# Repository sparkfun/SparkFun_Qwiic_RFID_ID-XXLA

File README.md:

SparkFun Qwiic RFID ID-XXLA
========================================

<table class="table table-hover table-striped table-bordered">
  <tr align="center">
   <td></td>
   <td></td>
  </tr>
  <tr align="center">
    <td><i>SparkFun RFID Qwiic Reader [<a href="https://www.sparkfun.com/products/15191">SEN-15191</a>]</i></td>
    <td><i>SparkFun RFID Qwiic Reader Kit [<a href="https://www.sparkfun.com/products/15209">KIT-15209</a>]<i></td>
  </tr>
</table>
     
The SparkFun Qwiic RFID ID-XXLA is a simple board that pairs with the ID-3LA, ID-12LA, ID-20LA, RFID modules.Utilizing the onboard ATtiny84A, the Qwiic RFID takes the six byte ID tag of your 125Khz RFID card, attaches a time stamp to it, and puts it onto a stack that holds up to 20 unique RFID scans at any given time. This information is easy to get at with some simple I2C commands and we’ve included some example code that shows you just how to do it using the broken out interrupt pin. We’ve also broken out two antennae pins that should only be used with the smaller ID-3LA.

The SparkFun Qwiic RFID has a buzzer and LED that indicates that card has been scanned. We’ve included a jumper to disconnect the buzzer, a jumper for the I2C pull-up resistors, an interrupt jumper, and finally an address jumper. The Qwiic RFID comes fully decked out in Qwiic connectors, no need to solder a thing, just plug it in and start scanning!

Repository Contents
-------------------

* **/Firmware** - The core sketch that runs the SparkFun Qwiic RFID ID-XXLA
* **/Arduino Examples** - A number of examples to show how to read buttons with time, change the I2C address and scan for I2C devices
* **/ATtiny Firmware** - Default firmware for the Qwiic RFID
* **/Hardware** - Eagle design files (.brd, .sch)

Documentation
--------------

* **[Hookup Guide](https://learn.sparkfun.com/tutorials/sparkfun-qwiic-rfid-idxxla-hookup-guide)** - Basic hookup guide.

Arduino Library 
----------------
* **[SparkFun Qwiic RFID Arduino Library](https://github.com/sparkfun/SparkFun_Qwiic_RFID_Arduino_Library)**

Python Package
----------------
* **[SparkFun Qwiic RFID Python Package](https://github.com/sparkfun/Qwiic_RFID_Py)**

Product Versions
----------------
* [SEN-15191](https://www.sparkfun.com/products/15191)- SparkFun Qwiic RFID ID-XXLA
* [KIT-15209](https://www.sparkfun.com/products/15209)- SparkFun Qwiic RFID ID-XXLA with ID Innovations RFID Module, Qwiic Cable, and RFID Tagged Cards, 

License Information
-------------------

This product is _**open source**_! 

Please review the LICENSE.md file for license information. 

If you have any questions or concerns on licensing, please contact techsupport@sparkfun.com.

Please use, reuse, and modify these files as you see fit. Please maintain attribution to SparkFun Electronics and release any derivative under the same license.

Distributed as-is; no warranty is given.

- Your friends at SparkFun.

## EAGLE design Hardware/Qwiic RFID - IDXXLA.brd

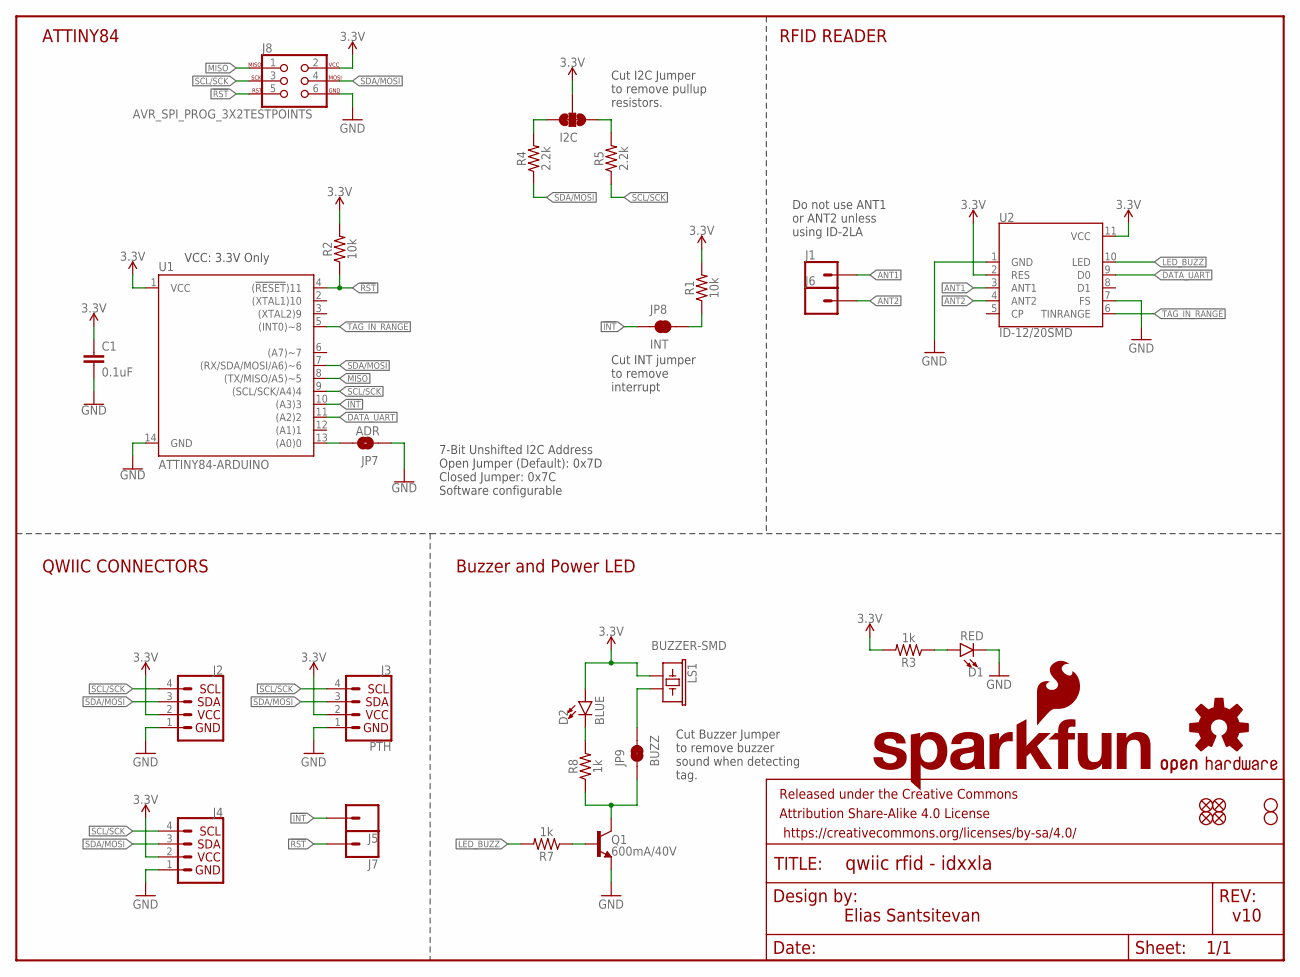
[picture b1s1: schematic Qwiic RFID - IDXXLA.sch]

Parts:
C1: 0.1uF; 0603
D1: RED; LED-0603
D2: BLUE; LED-0603
FRAME1: FRAME-LETTER; CREATIVE_COMMONS
I2C: JUMPER-SMT_3_2-NC_TRACE_SILK; SMT-JUMPER_3_2-NC_TRACE_SILK
J1, J5, J6, J7: CONN_01PTH_NO_SILK_YES_STOP; 1X01_NO_SILK
J2, J4: QWIIC_CONNECTORJS-1MM; 1X04_1MM_RA
J3: PTH; 1X04_NO_SILK
J8: AVR_SPI_PROG_3X2TESTPOINTS; 2X3_TEST_POINTS
JP1, JP2, JP5, JP6: FIDUCIALUFIDUCIAL; MICRO-FIDUCIAL
JP3, JP4: STAND-OFF
JP7: ADR; SMT-JUMPER_2_NO_SILK
JP8: INT; SMT-JUMPER_2_NC_TRACE_SILK
JP9: BUZZ; SMT-JUMPER_2_NC_TRACE_SILK
LOGO1: OSHW-LOGOMINI; OSHW-LOGO-MINI
LOGO3: SFE_LOGO_NAME_FLAME.1_INCH; SFE_LOGO_NAME_FLAME_.1
LS1: BUZZER-SMD; BUZZER-CCV
Q1: 600mA/40V; SOT23-3
R1, R2: 10k; 0603
R3, R7, R8: 1k; 0603
R4, R5: 2.2k; 0603
U1: ATTINY84-ARDUINO; SO14
U2: ID-12/20SMD; ID-12_SMD

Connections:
3.3V: C1.1, D2.A, I2C.2, J2.2, J3.2 (VCC), J4.2, J8.2, LS1.+ (1), R1.2, R2.2, R3.2, U1.1 (VCC), U2.2 (RES), U2.11 (VCC)
!INT: J5.1, JP8.1, U1.10 ((A3)3)
!RST: J7.1, J8.5, R2.1, U1.4 ((!RESET!)11)
ANT1: J1.1, U2.3 (ANT1)
ANT2: J6.1, U2.4 (ANT2)
DATA_UART: U1.11 ((A2)2), U2.9 (D0)
GND: C1.2, D1.C, J2.1, J3.1 (GND), J4.1, J8.6, JP7.1, Q1.2 (E), U1.14 (GND), U2.1 (GND), U2.7 (FS)
LED_BUZZ: R7.2, U2.10 (LED)
MISO: J8.1, U1.8 ((TX/MISO/A5)~5)
unnamed: I2C.1, R5.2
unnamed: I2C.3, R4.2
unnamed: D1.A, R3.1
unnamed: JP8.2, R1.1
unnamed: D2.C, R8.2
unnamed: JP7.2, U1.13 ((A0)0)
unnamed: Q1.1 (B), R7.1
unnamed: JP9.1, Q1.3 (C), R8.1
unnamed: JP9.2, LS1.- (2)
SCL/SCK: J2.4, J3.4 (SCL), J4.4, J8.3, R5.1, U1.9 ((SCL/SCK/A4)4)
SDA/MOSI: J2.3, J3.3 (SDA), J4.3, J8.4, R4.1, U1.7 ((RX/SDA/MOSI/A6)~6)
TAG_IN_RANGE: U1.5 ((INT0)~8), U2.6 (TINRANGE)

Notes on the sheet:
Buzzer and Power LED
RFID READER
ATTINY84
QWIIC CONNECTORS
7-Bit Unshifted I2C Address Open Jumper (Default): 0x7D Closed Jumper: 0x7C Software configurable
Cut Buzzer Jumper to remove buzzer sound when detecting tag.
Cut INT jumper to remove interrupt
Cut I2C Jumper to remove pullup resistors.
Do not use ANT1 or ANT2 unless using ID-2LA
v10
Elias Santsitevan
VCC: 3.3V Only

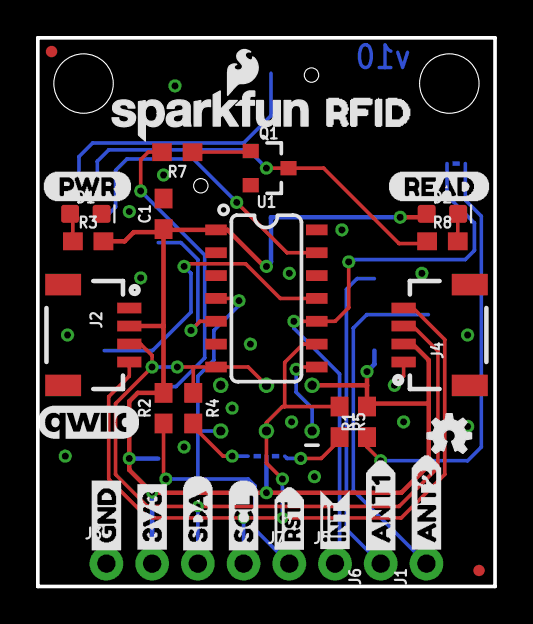
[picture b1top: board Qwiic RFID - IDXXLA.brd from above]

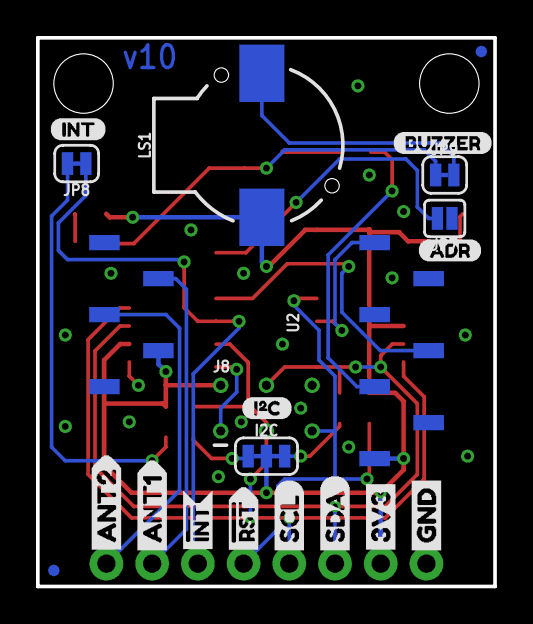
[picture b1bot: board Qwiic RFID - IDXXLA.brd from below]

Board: 2 copper layers, 25.4 x 30.5 mm, 59 parts (21 on the bottom side), 21 nets.

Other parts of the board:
U$1: QWIIC_COPYRIGHT_SMALL
U$2: I_SUPER2_C-()-03
U$3, U$17: ANT20
U$4: PWR-()-04
U$5, U$26: RST#-[>
U$6, U$23: SDA-[)
U$7, U$22: SCL-[)
U$8: RFID0
U$9, U$25: GND-04
U$10, U$24: 3V3-04
U$11, U$21: INT#-[<
U$12: ADR0
U$13: INT0
U$15: BUZZER0
U$16, U$20: ANT10
U$18: READ0

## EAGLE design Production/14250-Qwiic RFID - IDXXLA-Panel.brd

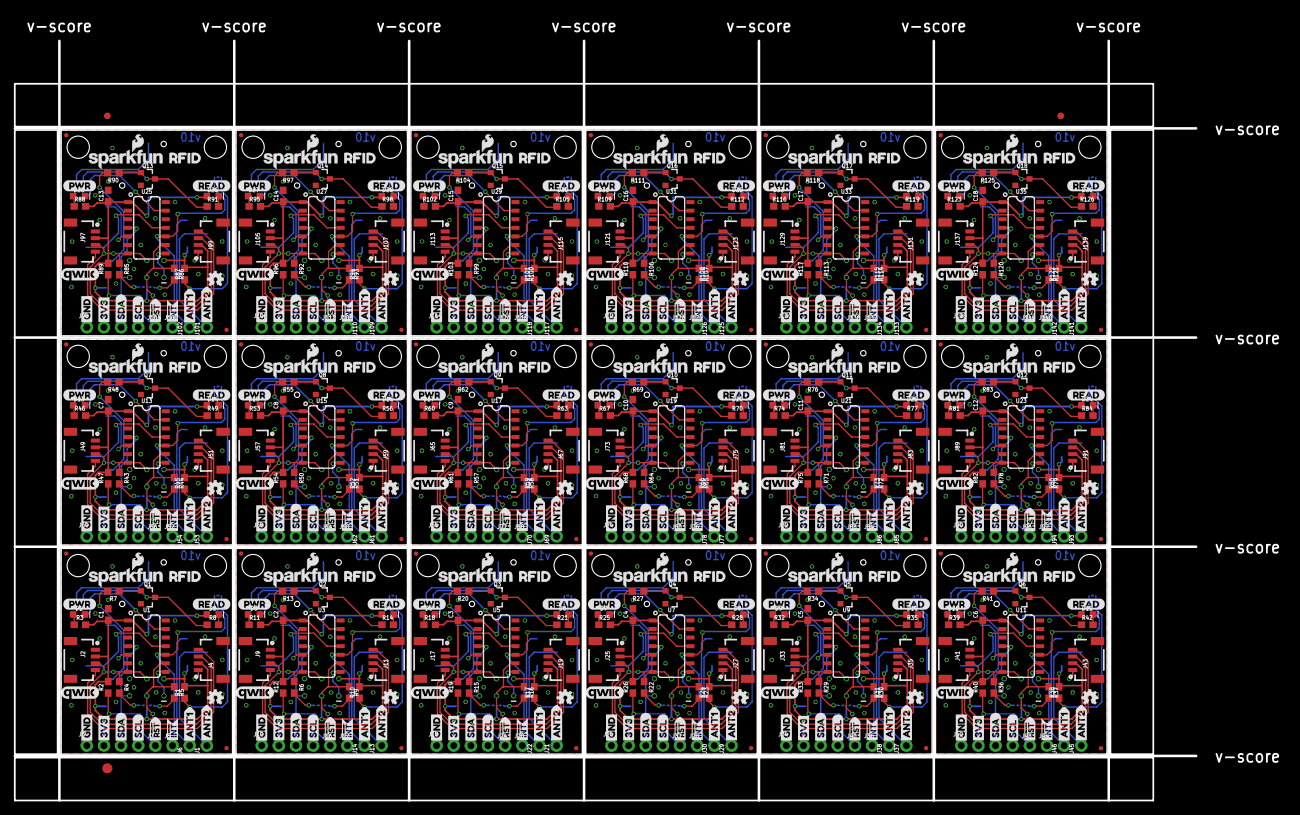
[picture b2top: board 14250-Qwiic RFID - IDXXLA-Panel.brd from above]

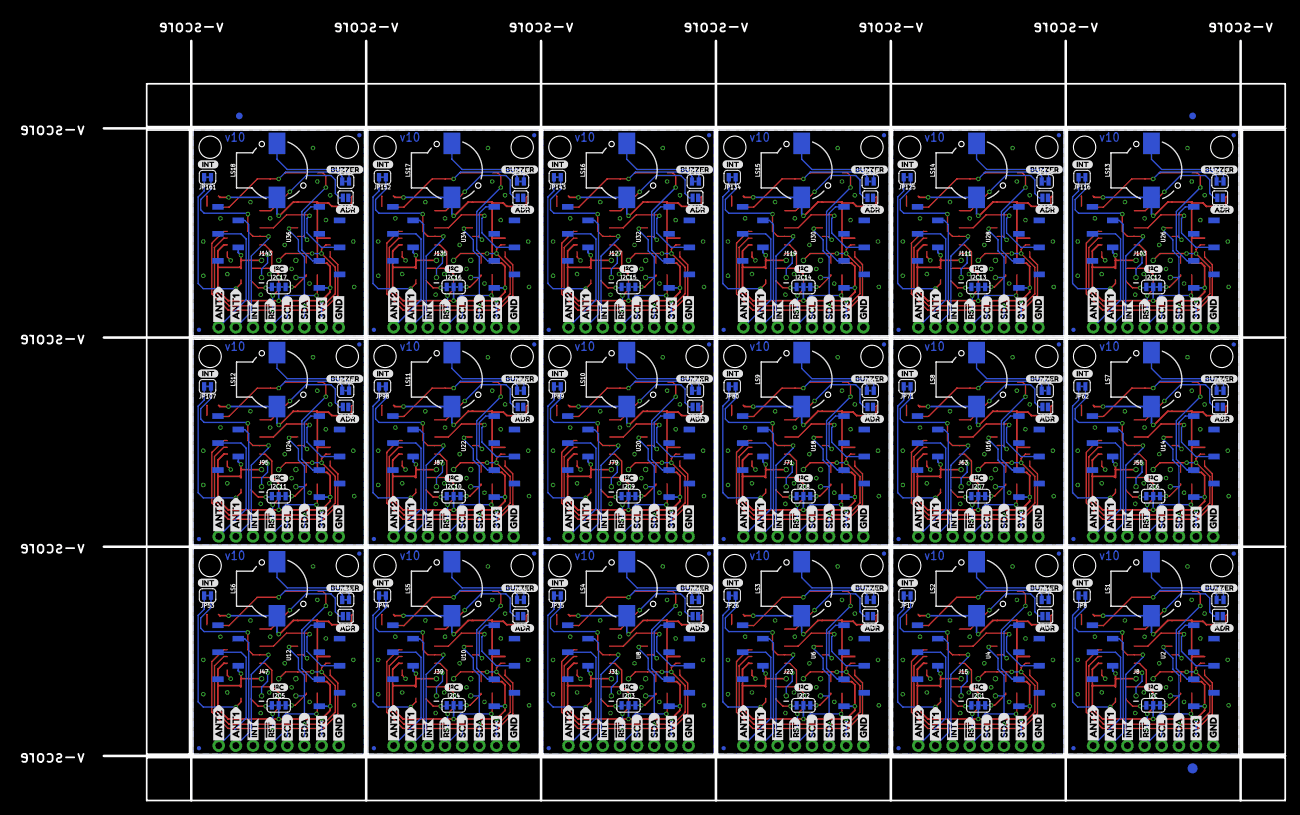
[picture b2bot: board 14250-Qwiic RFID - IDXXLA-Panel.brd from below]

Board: 2 copper layers, 188.2 x 116.4 mm, 1050 parts (381 on the bottom side), 378 nets.

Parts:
C1, C2, C3, C4, C5, C6, C7, C8, C9, C10, C11, C12, C13, C14, C15, C16, C17, C18: 0.1uF; 0603
D1, D3, D5, D7, D9, D11, D13, D15, D17, D19, D21, D23, D25, D27, D29, D31, D33, D35: RED; LED-0603
D2, D4, D6, D8, D10, D12, D14, D16, D18, D20, D22, D24, D26, D28, D30, D32, D34, D36: BLUE; LED-0603
E$1, E$2, E$3, E$4: FIDUCIAL-1X2
E$5, E$6: FIDUCIAL-1.5X3
I2C, I2C1, I2C2, I2C3, I2C4, I2C5, I2C6, I2C7, I2C8, I2C9, I2C10, I2C11, I2C12, I2C13, I2C14, I2C15, I2C16, I2C17: SMT-JUMPER_3_2-NC_TRACE_SILK
J1, J5, J6, J7, J12, J13, J14, J16, J20, J21, J22, J24, J28, J29, J30, J32, J36, J37, J38, J40, J44, J45, J46, J48, J52, J53, J54, J56, J60, J61, J62, J64, J68, J69, J70, J72, J76, J77, J78, J80, J84, J85, J86, J88, J92, J93, J94, J96, J100, J101, J102, J104, J108, J109, J110, J112, J116, J117, J118, J120, J124, J125, J126, J128, J132, J133, J134, J136, J140, J141, J142, J144: 1X01_NO_SILK
J2, J4, J9, J11, J17, J19, J25, J27, J33, J35, J41, J43, J49, J51, J57, J59, J65, J67, J73, J75, J81, J83, J89, J91, J97, J99, J105, J107, J113, J115, J121, J123, J129, J131, J137, J139: 1X04_1MM_RA
J3, J10, J18, J26, J34, J42, J50, J58, J66, J74, J82, J90, J98, J106, J114, J122, J130, J138: PTH; 1X04_NO_SILK
J8, J15, J23, J31, J39, J47, J55, J63, J71, J79, J87, J95, J103, J111, J119, J127, J135, J143: AVR_SPI_PROG_3X2TESTPOINTS; 2X3_TEST_POINTS
JP1, JP2, JP5, JP6, JP12, JP13, JP14, JP15, JP21, JP22, JP23, JP24, JP30, JP31, JP32, JP33, JP39, JP40, JP41, JP42, JP48, JP49, JP50, JP51, JP57, JP58, JP59, JP60, JP66, JP67, JP68, JP69, JP75, JP76, JP77, JP78, JP84, JP85, JP86, JP87, JP93, JP94, JP95, JP96, JP102, JP103, JP104, JP105, JP111, JP112, JP113, JP114, JP120, JP121, JP122, JP123, JP129, JP130, JP131, JP132, JP138, JP139, JP140, JP141, JP147, JP148, JP149, JP150, JP156, JP157, JP158, JP159: FIDUCIALUFIDUCIAL; MICRO-FIDUCIAL
JP3, JP4, JP10, JP11, JP19, JP20, JP28, JP29, JP37, JP38, JP46, JP47, JP55, JP56, JP64, JP65, JP73, JP74, JP82, JP83, JP91, JP92, JP100, JP101, JP109, JP110, JP118, JP119, JP127, JP128, JP136, JP137, JP145, JP146, JP154, JP155: STAND-OFF
JP7, JP16, JP25, JP34, JP43, JP52, JP61, JP70, JP79, JP88, JP97, JP106, JP115, JP124, JP133, JP142, JP151, JP160: ADR; SMT-JUMPER_2_NO_SILK
JP8, JP17, JP26, JP35, JP44, JP53, JP62, JP71, JP80, JP89, JP98, JP107, JP116, JP125, JP134, JP143, JP152, JP161: INT; SMT-JUMPER_2_NC_TRACE_SILK
JP9, JP18, JP27, JP36, JP45, JP54, JP63, JP72, JP81, JP90, JP99, JP108, JP117, JP126, JP135, JP144, JP153, JP162: BUZZ; SMT-JUMPER_2_NC_TRACE_SILK
LOGO1, LOGO2, LOGO5, LOGO7, LOGO9, LOGO11, LOGO13, LOGO15, LOGO17, LOGO19, LOGO21, LOGO23, LOGO25, LOGO27, LOGO29, LOGO31, LOGO33, LOGO35: OSHW-LOGOMINI; OSHW-LOGO-MINI
LOGO3, LOGO4, LOGO6, LOGO8, LOGO10, LOGO12, LOGO14, LOGO16, LOGO18, LOGO20, LOGO22, LOGO24, LOGO26, LOGO28, LOGO30, LOGO32, LOGO34, LOGO36: SFE_LOGO_NAME_FLAME.1_INCH; SFE_LOGO_NAME_FLAME_.1
LS1, LS2, LS3, LS4, LS5, LS6, LS7, LS8, LS9, LS10, LS11, LS12, LS13, LS14, LS15, LS16, LS17, LS18: BUZZER-SMD; BUZZER-CCV
Q1, Q2, Q3, Q4, Q5, Q6, Q7, Q8, Q9, Q10, Q11, Q12, Q13, Q14, Q15, Q16, Q17, Q18: 600mA/40V; SOT23-3
R1, R2, R10, R12, R17, R19, R24, R26, R31, R33, R38, R40, R45, R47, R52, R54, R59, R61, R66, R68, R73, R75, R80, R82, R87, R89, R94, R96, R101, R103, R108, R110, R115, R117, R122, R124: 10k; 0603
R3, R7, R8, R11, R13, R14, R18, R20, R21, R25, R27, R28, R32, R34, R35, R39, R41, R42, R46, R48, R49, R53, R55, R56, R60, R62, R63, R67, R69, R70, R74, R76, R77, R81, R83, R84, R88, R90, R91, R95, R97, R98, R102, R104, R105, R109, R111, R112, R116, R118, R119, R123, R125, R126: 1k; 0603
R4, R5, R6, R9, R15, R16, R22, R23, R29, R30, R36, R37, R43, R44, R50, R51, R57, R58, R64, R65, R71, R72, R78, R79, R85, R86, R92, R93, R99, R100, R106, R107, R113, R114, R120, R121: 2.2k; 0603
U1, U3, U5, U7, U9, U11, U13, U15, U17, U19, U21, U23, U25, U27, U29, U31, U33, U35: ATTINY84-ARDUINO; SO14
U2, U4, U6, U8, U10, U12, U14, U16, U18, U20, U22, U24, U26, U28, U30, U32, U34, U36: ID-12/20SMD; ID-12_SMD
U$1, U$47, U$71, U$95, U$119, U$143, U$167, U$191, U$215, U$239, U$263, U$287, U$311, U$335, U$359, U$383, U$407, U$431: QWIIC_COPYRIGHT_SMALL
U$2, U$43, U$67, U$91, U$115, U$139, U$163, U$187, U$211, U$235, U$259, U$283, U$307, U$331, U$355, U$379, U$403, U$427: I_SUPER2_C-()-03
U$3, U$17, U$33, U$35, U$57, U$59, U$81, U$83, U$105, U$107, U$129, U$131, U$153, U$155, U$177, U$179, U$201, U$203, U$225, U$227, U$249, U$251, U$273, U$275, U$297, U$299, U$321, U$323, U$345, U$347, U$369, U$371, U$393, U$395, U$417, U$419: ANT20
U$4, U$46, U$70, U$94, U$118, U$142, U$166, U$190, U$214, U$238, U$262, U$286, U$310, U$334, U$358, U$382, U$406, U$430: PWR-()-04
U$5, U$14, U$26, U$42, U$49, U$66, U$73, U$90, U$97, U$114, U$121, U$138, U$145, U$162, U$169, U$186, U$193, U$210, U$217, U$234, U$241, U$258, U$265, U$282, U$289, U$306, U$313, U$330, U$337, U$354, U$361, U$378, U$385, U$402, U$409, U$426: RST#-[>
U$6, U$19, U$23, U$39, U$50, U$63, U$74, U$87, U$98, U$111, U$122, U$135, U$146, U$159, U$170, U$183, U$194, U$207, U$218, U$231, U$242, U$255, U$266, U$279, U$290, U$303, U$314, U$327, U$338, U$351, U$362, U$375, U$386, U$399, U$410, U$423: SDA-[)
U$7, U$22, U$27, U$38, U$51, U$62, U$75, U$86, U$99, U$110, U$123, U$134, U$147, U$158, U$171, U$182, U$195, U$206, U$219, U$230, U$243, U$254, U$267, U$278, U$291, U$302, U$315, U$326, U$339, U$350, U$363, U$374, U$387, U$398, U$411, U$422: SCL-[)
U$8, U$48, U$72, U$96, U$120, U$144, U$168, U$192, U$216, U$240, U$264, U$288, U$312, U$336, U$360, U$384, U$408, U$432: RFID0
U$9, U$25, U$28, U$41, U$52, U$65, U$76, U$89, U$100, U$113, U$124, U$137, U$148, U$161, U$172, U$185, U$196, U$209, U$220, U$233, U$244, U$257, U$268, U$281, U$292, U$305, U$316, U$329, U$340, U$353, U$364, U$377, U$388, U$401, U$412, U$425: GND-04
U$10, U$24, U$29, U$40, U$53, U$64, U$77, U$88, U$101, U$112, U$125, U$136, U$149, U$160, U$173, U$184, U$197, U$208, U$221, U$232, U$245, U$256, U$269, U$280, U$293, U$304, U$317, U$328, U$341, U$352, U$365, U$376, U$389, U$400, U$413, U$424: 3V3-04
U$11, U$21, U$30, U$37, U$54, U$61, U$78, U$85, U$102, U$109, U$126, U$133, U$150, U$157, U$174, U$181, U$198, U$205, U$222, U$229, U$246, U$253, U$270, U$277, U$294, U$301, U$318, U$325, U$342, U$349, U$366, U$373, U$390, U$397, U$414, U$421: INT#-[<
U$12, U$44, U$68, U$92, U$116, U$140, U$164, U$188, U$212, U$236, U$260, U$284, U$308, U$332, U$356, U$380, U$404, U$428: ADR0
U$13, U$45, U$69, U$93, U$117, U$141, U$165, U$189, U$213, U$237, U$261, U$285, U$309, U$333, U$357, U$381, U$405, U$429: INT0
U$15, U$31, U$55, U$79, U$103, U$127, U$151, U$175, U$199, U$223, U$247, U$271, U$295, U$319, U$343, U$367, U$391, U$415: BUZZER0
U$16, U$20, U$32, U$36, U$56, U$60, U$80, U$84, U$104, U$108, U$128, U$132, U$152, U$156, U$176, U$180, U$200, U$204, U$224, U$228, U$248, U$252, U$272, U$276, U$296, U$300, U$320, U$324, U$344, U$348, U$368, U$372, U$392, U$396, U$416, U$420: ANT10
U$18, U$34, U$58, U$82, U$106, U$130, U$154, U$178, U$202, U$226, U$250, U$274, U$298, U$322, U$346, U$370, U$394, U$418: READ0

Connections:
3.3V: C1.1, D2.A, I2C.2, J2.2, J3.2, J4.2, J8.2, LS1.+, R1.2, R2.2, R3.2, U1.1, U2.2, U2.11
3.3V1: C2.1, D4.A, I2C1.2, J9.2, J10.2, J11.2, J15.2, LS2.+, R10.2, R11.2, R12.2, U3.1, U4.2, U4.11
3.3V2: C3.1, D6.A, I2C2.2, J17.2, J18.2, J19.2, J23.2, LS3.+, R17.2, R18.2, R19.2, U5.1, U6.2, U6.11
3.3V3: C4.1, D8.A, I2C3.2, J25.2, J26.2, J27.2, J31.2, LS4.+, R24.2, R25.2, R26.2, U7.1, U8.2, U8.11
3.3V4: C5.1, D10.A, I2C4.2, J33.2, J34.2, J35.2, J39.2, LS5.+, R31.2, R32.2, R33.2, U9.1, U10.2, U10.11
3.3V5: C6.1, D12.A, I2C5.2, J41.2, J42.2, J43.2, J47.2, LS6.+, R38.2, R39.2, R40.2, U11.1, U12.2, U12.11
3.3V6: C7.1, D14.A, I2C6.2, J49.2, J50.2, J51.2, J55.2, LS7.+, R45.2, R46.2, R47.2, U13.1, U14.2, U14.11
3.3V7: C8.1, D16.A, I2C7.2, J57.2, J58.2, J59.2, J63.2, LS8.+, R52.2, R53.2, R54.2, U15.1, U16.2, U16.11
3.3V8: C9.1, D18.A, I2C8.2, J65.2, J66.2, J67.2, J71.2, LS9.+, R59.2, R60.2, R61.2, U17.1, U18.2, U18.11
3.3V9: C10.1, D20.A, I2C9.2, J73.2, J74.2, J75.2, J79.2, LS10.+, R66.2, R67.2, R68.2, U19.1, U20.2, U20.11
3.3V10: C11.1, D22.A, I2C10.2, J81.2, J82.2, J83.2, J87.2, LS11.+, R73.2, R74.2, R75.2, U21.1, U22.2, U22.11
3.3V11: C12.1, D24.A, I2C11.2, J89.2, J90.2, J91.2, J95.2, LS12.+, R80.2, R81.2, R82.2, U23.1, U24.2, U24.11
3.3V12: C13.1, D26.A, I2C12.2, J97.2, J98.2, J99.2, J103.2, LS13.+, R87.2, R88.2, R89.2, U25.1, U26.2, U26.11
3.3V13: C14.1, D28.A, I2C13.2, J105.2, J106.2, J107.2, J111.2, LS14.+, R94.2, R95.2, R96.2, U27.1, U28.2, U28.11
3.3V14: C15.1, D30.A, I2C14.2, J113.2, J114.2, J115.2, J119.2, LS15.+, R101.2, R102.2, R103.2, U29.1, U30.2, U30.11
3.3V15: C16.1, D32.A, I2C15.2, J121.2, J122.2, J123.2, J127.2, LS16.+, R108.2, R109.2, R110.2, U31.1, U32.2, U32.11
3.3V16: C17.1, D34.A, I2C16.2, J129.2, J130.2, J131.2, J135.2, LS17.+, R115.2, R116.2, R117.2, U33.1, U34.2, U34.11
3.3V17: C18.1, D36.A, I2C17.2, J137.2, J138.2, J139.2, J143.2, LS18.+, R122.2, R123.2, R124.2, U35.1, U36.2, U36.11
!INT: J5.1, JP8.1, U1.10
!INT1: J12.1, JP17.1, U3.10
!INT2: J20.1, JP26.1, U5.10
!INT3: J28.1, JP35.1, U7.10
!INT4: J36.1, JP44.1, U9.10
!INT5: J44.1, JP53.1, U11.10
!INT6: J52.1, JP62.1, U13.10
!INT7: J60.1, JP71.1, U15.10
!INT8: J68.1, JP80.1, U17.10
!INT9: J76.1, JP89.1, U19.10
!INT10: J84.1, JP98.1, U21.10
!INT11: J92.1, JP107.1, U23.10
!INT12: J100.1, JP116.1, U25.10
!INT13: J108.1, JP125.1, U27.10
!INT14: J116.1, JP134.1, U29.10
!INT15: J124.1, JP143.1, U31.10
!INT16: J132.1, JP152.1, U33.10
!INT17: J140.1, JP161.1, U35.10
!RST: J7.1, J8.5, R2.1, U1.4
!RST1: J15.5, J16.1, R12.1, U3.4
!RST2: J23.5, J24.1, R19.1, U5.4
!RST3: J31.5, J32.1, R26.1, U7.4
!RST4: J39.5, J40.1, R33.1, U9.4
!RST5: J47.5, J48.1, R40.1, U11.4
!RST6: J55.5, J56.1, R47.1, U13.4
!RST7: J63.5, J64.1, R54.1, U15.4
!RST8: J71.5, J72.1, R61.1, U17.4
!RST9: J79.5, J80.1, R68.1, U19.4
!RST10: J87.5, J88.1, R75.1, U21.4
!RST11: J95.5, J96.1, R82.1, U23.4
!RST12: J103.5, J104.1, R89.1, U25.4
!RST13: J111.5, J112.1, R96.1, U27.4
!RST14: J119.5, J120.1, R103.1, U29.4
!RST15: J127.5, J128.1, R110.1, U31.4
!RST16: J135.5, J136.1, R117.1, U33.4
!RST17: J143.5, J144.1, R124.1, U35.4
ANT1: J1.1, U2.3
ANT2: J6.1, U2.4
ANT3: J13.1, U4.3
ANT4: J14.1, U4.4
ANT5: J21.1, U6.3
ANT6: J22.1, U6.4
ANT7: J29.1, U8.3
ANT8: J30.1, U8.4
ANT9: J37.1, U10.3
ANT10: J38.1, U10.4
ANT11: J45.1, U12.3
ANT12: J46.1, U12.4
ANT13: J53.1, U14.3
ANT14: J54.1, U14.4
ANT15: J61.1, U16.3
ANT16: J62.1, U16.4
ANT17: J69.1, U18.3
ANT18: J70.1, U18.4
ANT19: J77.1, U20.3
ANT20: J78.1, U20.4
ANT21: J85.1, U22.3
ANT22: J86.1, U22.4
ANT23: J93.1, U24.3
ANT24: J94.1, U24.4
ANT25: J101.1, U26.3
ANT26: J102.1, U26.4
ANT27: J109.1, U28.3
ANT28: J110.1, U28.4
ANT29: J117.1, U30.3
ANT30: J118.1, U30.4
ANT31: J125.1, U32.3
ANT32: J126.1, U32.4
ANT33: J133.1, U34.3
ANT34: J134.1, U34.4
ANT35: J141.1, U36.3
ANT36: J142.1, U36.4
DATA_UART: U1.11, U2.9
DATA_UART1: U3.11, U4.9
DATA_UART2: U5.11, U6.9
DATA_UART3: U7.11, U8.9
DATA_UART4: U9.11, U10.9
DATA_UART5: U11.11, U12.9
DATA_UART6: U13.11, U14.9
DATA_UART7: U15.11, U16.9
DATA_UART8: U17.11, U18.9
DATA_UART9: U19.11, U20.9
DATA_UART10: U21.11, U22.9
DATA_UART11: U23.11, U24.9
DATA_UART12: U25.11, U26.9
DATA_UART13: U27.11, U28.9
DATA_UART14: U29.11, U30.9
DATA_UART15: U31.11, U32.9
DATA_UART16: U33.11, U34.9
DATA_UART17: U35.11, U36.9
GND: C1.2, D1.C, J2.1, J3.1, J4.1, J8.6, JP7.1, Q1.2, U1.14, U2.1, U2.7
GND1: C2.2, D3.C, J9.1, J10.1, J11.1, J15.6, JP16.1, Q2.2, U3.14, U4.1, U4.7
GND2: C3.2, D5.C, J17.1, J18.1, J19.1, J23.6, JP25.1, Q3.2, U5.14, U6.1, U6.7
GND3: C4.2, D7.C, J25.1, J26.1, J27.1, J31.6, JP34.1, Q4.2, U7.14, U8.1, U8.7
GND4: C5.2, D9.C, J33.1, J34.1, J35.1, J39.6, JP43.1, Q5.2, U9.14, U10.1, U10.7
GND5: C6.2, D11.C, J41.1, J42.1, J43.1, J47.6, JP52.1, Q6.2, U11.14, U12.1, U12.7
GND6: C7.2, D13.C, J49.1, J50.1, J51.1, J55.6, JP61.1, Q7.2, U13.14, U14.1, U14.7
GND7: C8.2, D15.C, J57.1, J58.1, J59.1, J63.6, JP70.1, Q8.2, U15.14, U16.1, U16.7
GND8: C9.2, D17.C, J65.1, J66.1, J67.1, J71.6, JP79.1, Q9.2, U17.14, U18.1, U18.7
GND9: C10.2, D19.C, J73.1, J74.1, J75.1, J79.6, JP88.1, Q10.2, U19.14, U20.1, U20.7
GND10: C11.2, D21.C, J81.1, J82.1, J83.1, J87.6, JP97.1, Q11.2, U21.14, U22.1, U22.7
GND11: C12.2, D23.C, J89.1, J90.1, J91.1, J95.6, JP106.1, Q12.2, U23.14, U24.1, U24.7
GND12: C13.2, D25.C, J97.1, J98.1, J99.1, J103.6, JP115.1, Q13.2, U25.14, U26.1, U26.7
GND13: C14.2, D27.C, J105.1, J106.1, J107.1, J111.6, JP124.1, Q14.2, U27.14, U28.1, U28.7
GND14: C15.2, D29.C, J113.1, J114.1, J115.1, J119.6, JP133.1, Q15.2, U29.14, U30.1, U30.7
GND15: C16.2, D31.C, J121.1, J122.1, J123.1, J127.6, JP142.1, Q16.2, U31.14, U32.1, U32.7
GND16: C17.2, D33.C, J129.1, J130.1, J131.1, J135.6, JP151.1, Q17.2, U33.14, U34.1, U34.7
GND17: C18.2, D35.C, J137.1, J138.1, J139.1, J143.6, JP160.1, Q18.2, U35.14, U36.1, U36.7
LED_BUZZ: R7.2, U2.10
LED_BUZZ1: R13.2, U4.10
LED_BUZZ2: R20.2, U6.10
LED_BUZZ3: R27.2, U8.10
LED_BUZZ4: R34.2, U10.10
LED_BUZZ5: R41.2, U12.10
LED_BUZZ6: R48.2, U14.10
LED_BUZZ7: R55.2, U16.10
LED_BUZZ8: R62.2, U18.10
LED_BUZZ9: R69.2, U20.10
LED_BUZZ10: R76.2, U22.10
LED_BUZZ11: R83.2, U24.10
LED_BUZZ12: R90.2, U26.10
LED_BUZZ13: R97.2, U28.10
LED_BUZZ14: R104.2, U30.10
LED_BUZZ15: R111.2, U32.10
LED_BUZZ16: R118.2, U34.10
LED_BUZZ17: R125.2, U36.10
MISO: J8.1, U1.8
MISO1: J15.1, U3.8
MISO2: J23.1, U5.8
MISO3: J31.1, U7.8
MISO4: J39.1, U9.8
MISO5: J47.1, U11.8
MISO6: J55.1, U13.8
MISO7: J63.1, U15.8
MISO8: J71.1, U17.8
MISO9: J79.1, U19.8
MISO10: J87.1, U21.8
MISO11: J95.1, U23.8
MISO12: J103.1, U25.8
MISO13: J111.1, U27.8
MISO14: J119.1, U29.8
MISO15: J127.1, U31.8
MISO16: J135.1, U33.8
MISO17: J143.1, U35.8
unnamed: I2C.1, R5.2
unnamed: I2C.3, R4.2
unnamed: D1.A, R3.1
unnamed: JP8.2, R1.1
unnamed: D2.C, R8.2
unnamed: JP7.2, U1.13
unnamed: Q1.1, R7.1
unnamed: JP9.1, Q1.3, R8.1
unnamed: JP9.2, LS1.-
unnamed: I2C1.1, R9.2
unnamed: D3.A, R11.1
unnamed: JP16.2, U3.13
unnamed: I2C1.3, R6.2
unnamed: JP17.2, R10.1
unnamed: Q2.1, R13.1
unnamed: JP18.1, Q2.3, R14.1
unnamed: D4.C, R14.2
unnamed: JP18.2, LS2.-
unnamed: I2C2.1, R16.2
unnamed: D5.A, R18.1
unnamed: JP25.2, U5.13
unnamed: I2C2.3, R15.2
unnamed: JP26.2, R17.1
unnamed: Q3.1, R20.1
unnamed: JP27.1, Q3.3, R21.1
unnamed: D6.C, R21.2
unnamed: JP27.2, LS3.-
unnamed: I2C3.1, R23.2
unnamed: D7.A, R25.1
unnamed: JP34.2, U7.13
unnamed: I2C3.3, R22.2
unnamed: JP35.2, R24.1
unnamed: Q4.1, R27.1
unnamed: JP36.1, Q4.3, R28.1
unnamed: D8.C, R28.2
unnamed: JP36.2, LS4.-
unnamed: I2C4.1, R30.2
unnamed: D9.A, R32.1
unnamed: JP43.2, U9.13
unnamed: I2C4.3, R29.2
unnamed: JP44.2, R31.1
unnamed: Q5.1, R34.1
unnamed: JP45.1, Q5.3, R35.1
unnamed: D10.C, R35.2
unnamed: JP45.2, LS5.-
unnamed: I2C5.1, R37.2
unnamed: D11.A, R39.1
unnamed: JP52.2, U11.13
unnamed: I2C5.3, R36.2
unnamed: JP53.2, R38.1
unnamed: Q6.1, R41.1
unnamed: JP54.1, Q6.3, R42.1
unnamed: D12.C, R42.2
unnamed: JP54.2, LS6.-
unnamed: I2C6.1, R44.2
unnamed: D13.A, R46.1
unnamed: JP61.2, U13.13
unnamed: I2C6.3, R43.2
unnamed: JP62.2, R45.1
unnamed: Q7.1, R48.1
unnamed: JP63.1, Q7.3, R49.1
unnamed: D14.C, R49.2
unnamed: JP63.2, LS7.-
unnamed: I2C7.1, R51.2
unnamed: D15.A, R53.1
unnamed: JP70.2, U15.13
unnamed: I2C7.3, R50.2
unnamed: JP71.2, R52.1
unnamed: Q8.1, R55.1
unnamed: JP72.1, Q8.3, R56.1
unnamed: D16.C, R56.2
unnamed: JP72.2, LS8.-
unnamed: I2C8.1, R58.2
unnamed: D17.A, R60.1
unnamed: JP79.2, U17.13
unnamed: I2C8.3, R57.2
unnamed: JP80.2, R59.1
unnamed: Q9.1, R62.1
unnamed: JP81.1, Q9.3, R63.1
unnamed: D18.C, R63.2
unnamed: JP81.2, LS9.-
unnamed: I2C9.1, R65.2
unnamed: D19.A, R67.1
unnamed: JP88.2, U19.13
unnamed: I2C9.3, R64.2
unnamed: JP89.2, R66.1
unnamed: Q10.1, R69.1
unnamed: JP90.1, Q10.3, R70.1
unnamed: D20.C, R70.2
unnamed: JP90.2, LS10.-
unnamed: I2C10.1, R72.2
unnamed: D21.A, R74.1
unnamed: JP97.2, U21.13
unnamed: I2C10.3, R71.2
unnamed: JP98.2, R73.1
unnamed: Q11.1, R76.1
unnamed: JP99.1, Q11.3, R77.1
unnamed: D22.C, R77.2
unnamed: JP99.2, LS11.-
unnamed: I2C11.1, R79.2
unnamed: D23.A, R81.1
unnamed: JP106.2, U23.13
unnamed: I2C11.3, R78.2
unnamed: JP107.2, R80.1
unnamed: Q12.1, R83.1
unnamed: JP108.1, Q12.3, R84.1
unnamed: D24.C, R84.2
unnamed: JP108.2, LS12.-
unnamed: I2C12.1, R86.2
unnamed: D25.A, R88.1
unnamed: JP115.2, U25.13
unnamed: I2C12.3, R85.2
unnamed: JP116.2, R87.1
unnamed: Q13.1, R90.1
unnamed: JP117.1, Q13.3, R91.1
unnamed: D26.C, R91.2
unnamed: JP117.2, LS13.-
unnamed: I2C13.1, R93.2
unnamed: D27.A, R95.1
unnamed: JP124.2, U27.13
unnamed: I2C13.3, R92.2
unnamed: JP125.2, R94.1
unnamed: Q14.1, R97.1
unnamed: JP126.1, Q14.3, R98.1
unnamed: D28.C, R98.2
unnamed: JP126.2, LS14.-
unnamed: I2C14.1, R100.2
unnamed: D29.A, R102.1
unnamed: JP133.2, U29.13
unnamed: I2C14.3, R99.2
unnamed: JP134.2, R101.1
unnamed: Q15.1, R104.1
unnamed: JP135.1, Q15.3, R105.1
unnamed: D30.C, R105.2
unnamed: JP135.2, LS15.-
unnamed: I2C15.1, R107.2
unnamed: D31.A, R109.1
unnamed: JP142.2, U31.13
unnamed: I2C15.3, R106.2
unnamed: JP143.2, R108.1
unnamed: Q16.1, R111.1
unnamed: JP144.1, Q16.3, R112.1
unnamed: D32.C, R112.2
unnamed: JP144.2, LS16.-
unnamed: I2C16.1, R114.2
unnamed: D33.A, R116.1
unnamed: JP151.2, U33.13
unnamed: I2C16.3, R113.2
unnamed: JP152.2, R115.1
unnamed: Q17.1, R118.1
unnamed: JP153.1, Q17.3, R119.1
unnamed: D34.C, R119.2
unnamed: JP153.2, LS17.-
unnamed: I2C17.1, R121.2
unnamed: D35.A, R123.1
unnamed: JP160.2, U35.13
unnamed: I2C17.3, R120.2
unnamed: JP161.2, R122.1
unnamed: Q18.1, R125.1
unnamed: JP162.1, Q18.3, R126.1
unnamed: D36.C, R126.2
unnamed: JP162.2, LS18.-
SCL/SCK: J2.4, J3.4, J4.4, J8.3, R5.1, U1.9
SCL/SCK1: J9.4, J10.4, J11.4, J15.3, R9.1, U3.9
SCL/SCK2: J17.4, J18.4, J19.4, J23.3, R16.1, U5.9
SCL/SCK3: J25.4, J26.4, J27.4, J31.3, R23.1, U7.9
SCL/SCK4: J33.4, J34.4, J35.4, J39.3, R30.1, U9.9
SCL/SCK5: J41.4, J42.4, J43.4, J47.3, R37.1, U11.9
SCL/SCK6: J49.4, J50.4, J51.4, J55.3, R44.1, U13.9
SCL/SCK7: J57.4, J58.4, J59.4, J63.3, R51.1, U15.9
SCL/SCK8: J65.4, J66.4, J67.4, J71.3, R58.1, U17.9
SCL/SCK9: J73.4, J74.4, J75.4, J79.3, R65.1, U19.9
SCL/SCK10: J81.4, J82.4, J83.4, J87.3, R72.1, U21.9
SCL/SCK11: J89.4, J90.4, J91.4, J95.3, R79.1, U23.9
SCL/SCK12: J97.4, J98.4, J99.4, J103.3, R86.1, U25.9
SCL/SCK13: J105.4, J106.4, J107.4, J111.3, R93.1, U27.9
SCL/SCK14: J113.4, J114.4, J115.4, J119.3, R100.1, U29.9
SCL/SCK15: J121.4, J122.4, J123.4, J127.3, R107.1, U31.9
SCL/SCK16: J129.4, J130.4, J131.4, J135.3, R114.1, U33.9
SCL/SCK17: J137.4, J138.4, J139.4, J143.3, R121.1, U35.9
SDA/MOSI: J2.3, J3.3, J4.3, J8.4, R4.1, U1.7
SDA/MOSI1: J9.3, J10.3, J11.3, J15.4, R6.1, U3.7
SDA/MOSI2: J17.3, J18.3, J19.3, J23.4, R15.1, U5.7
SDA/MOSI3: J25.3, J26.3, J27.3, J31.4, R22.1, U7.7
SDA/MOSI4: J33.3, J34.3, J35.3, J39.4, R29.1, U9.7
SDA/MOSI5: J41.3, J42.3, J43.3, J47.4, R36.1, U11.7
SDA/MOSI6: J49.3, J50.3, J51.3, J55.4, R43.1, U13.7
SDA/MOSI7: J57.3, J58.3, J59.3, J63.4, R50.1, U15.7
SDA/MOSI8: J65.3, J66.3, J67.3, J71.4, R57.1, U17.7
SDA/MOSI9: J73.3, J74.3, J75.3, J79.4, R64.1, U19.7
SDA/MOSI10: J81.3, J82.3, J83.3, J87.4, R71.1, U21.7
SDA/MOSI11: J89.3, J90.3, J91.3, J95.4, R78.1, U23.7
SDA/MOSI12: J97.3, J98.3, J99.3, J103.4, R85.1, U25.7
SDA/MOSI13: J105.3, J106.3, J107.3, J111.4, R92.1, U27.7
SDA/MOSI14: J113.3, J114.3, J115.3, J119.4, R99.1, U29.7
SDA/MOSI15: J121.3, J122.3, J123.3, J127.4, R106.1, U31.7
SDA/MOSI16: J129.3, J130.3, J131.3, J135.4, R113.1, U33.7
SDA/MOSI17: J137.3, J138.3, J139.3, J143.4, R120.1, U35.7
TAG_IN_RANGE: U1.5, U2.6
TAG_IN_RANGE1: U3.5, U4.6
TAG_IN_RANGE2: U5.5, U6.6
TAG_IN_RANGE3: U7.5, U8.6
TAG_IN_RANGE4: U9.5, U10.6
TAG_IN_RANGE5: U11.5, U12.6
TAG_IN_RANGE6: U13.5, U14.6
TAG_IN_RANGE7: U15.5, U16.6
TAG_IN_RANGE8: U17.5, U18.6
TAG_IN_RANGE9: U19.5, U20.6
TAG_IN_RANGE10: U21.5, U22.6
TAG_IN_RANGE11: U23.5, U24.6
TAG_IN_RANGE12: U25.5, U26.6
TAG_IN_RANGE13: U27.5, U28.6
TAG_IN_RANGE14: U29.5, U30.6
TAG_IN_RANGE15: U31.5, U32.6
TAG_IN_RANGE16: U33.5, U34.6
TAG_IN_RANGE17: U35.5, U36.6

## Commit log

2019-01-08 Initial Commit (copy from Qwiic RFID)
2019-01-15 Updates general trace layout, moves interrupt jumper to upper right, moves stat LED to TOP layer parallel with PWR LED
    * Adds SparkFun Flame and removes SparkX references
    * Changes version
    * Updates text to vector in schematic.
    * Updates Qwiic_RFID silk and power LED to something larger.
2019-01-16 Adds better SparkFun silk, changes text to vector, and updates product name silk
2019-01-16 Changes sparkFun logo to sparkFun + flame logo, adds dimensions for standoffs
2019-01-17 Created panel V10
2019-01-29 Updates example firmware with better comments and more expressive code
2019-01-29 Removes BYTE_REQUEST variable and replaces with the correct one: TAG_REQUEST
2019-01-29 Updates panel to add TSTOP to MISO via on the ISP header.
2019-02-26 Updates the readme from its SparkX counterpart to a SparkFun readme
2019-02-28 New Folders
    -Move Arduino examples into firmware folder
    -Include separate folder for the Qwiic RFID's default firmware
2019-03-22 Removes reference to SparkX
2019-07-08 Removes example code and add link to Arduino Library in Readme
2019-07-08 Fixes highlight in Readme
2021-02-02 Updates default i2c address for the Qwiic RFID to 0x13 as it was using an "illegal" address used for 10-bit addressing.
2021-02-02 Updates firmware to check default address against what's in memory
2021-02-02 Revert "Updates firmware to check default address against what's in memory"
    This reverts commit bb3fbe052572b12ccae124712ce3d4e583919edf.
2021-02-24 Update README.md
    Add link for python package
2021-02-24 Update README.md
    fix formatting
2023-12-07 Replaces old binary with new one
2024-11-26 Update Schematic to Reflect I2C Address Change
2025-07-15 Changes post-increment to a pre-increment
    The comparison checking whether the array is at the end its' length was
    incrementing the current value after doing the comparison
    (post-increment). This resulted in assigning values outside the bounds
    of the array.
2025-07-28 Rebuilds firmware, fixes name of folder to correctly reflect the processor
2025-07-29 Removes many unnecessary files and nesting, moves documents out to the main parent folder

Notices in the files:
parts and their libraries:
SparkFun-Resistors: Licensing: Creative Commons ShareAlike 4.0 International - https://creativecommons.org/licenses/by-sa/4.0
SparkFun-Aesthetics: Released under the Creative Commons Attribution Share-Alike 4.0 License
SparkFun-Aesthetics: https://creativecommons.org/licenses/by-sa/4.0
